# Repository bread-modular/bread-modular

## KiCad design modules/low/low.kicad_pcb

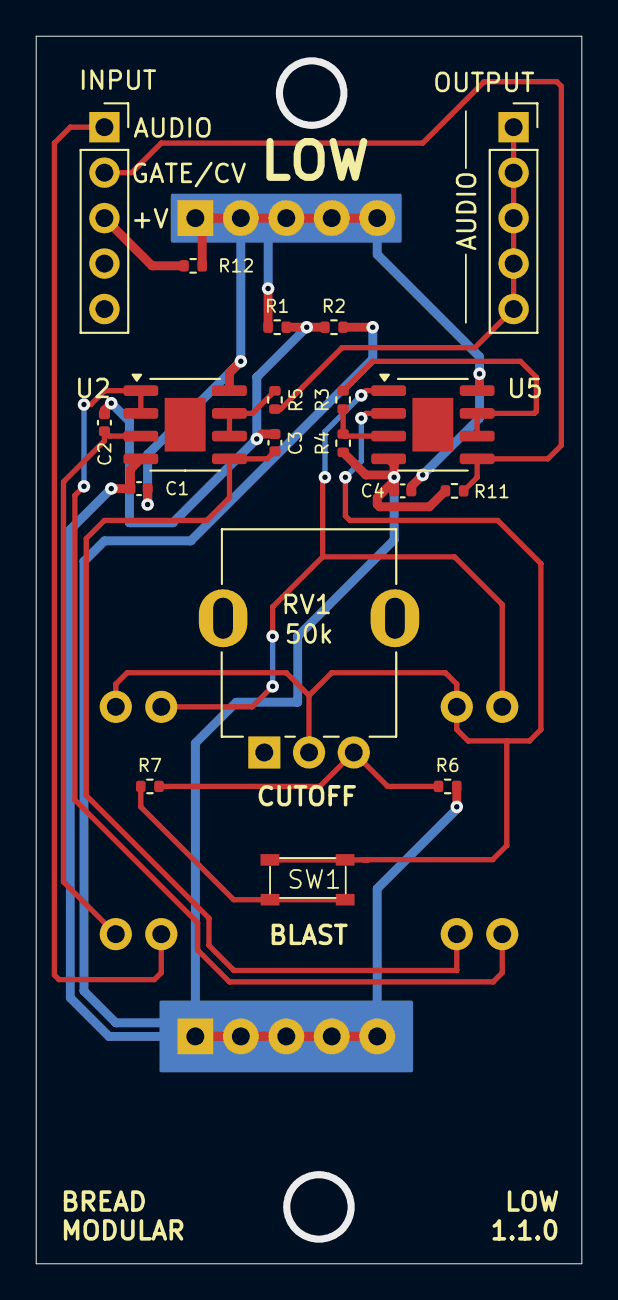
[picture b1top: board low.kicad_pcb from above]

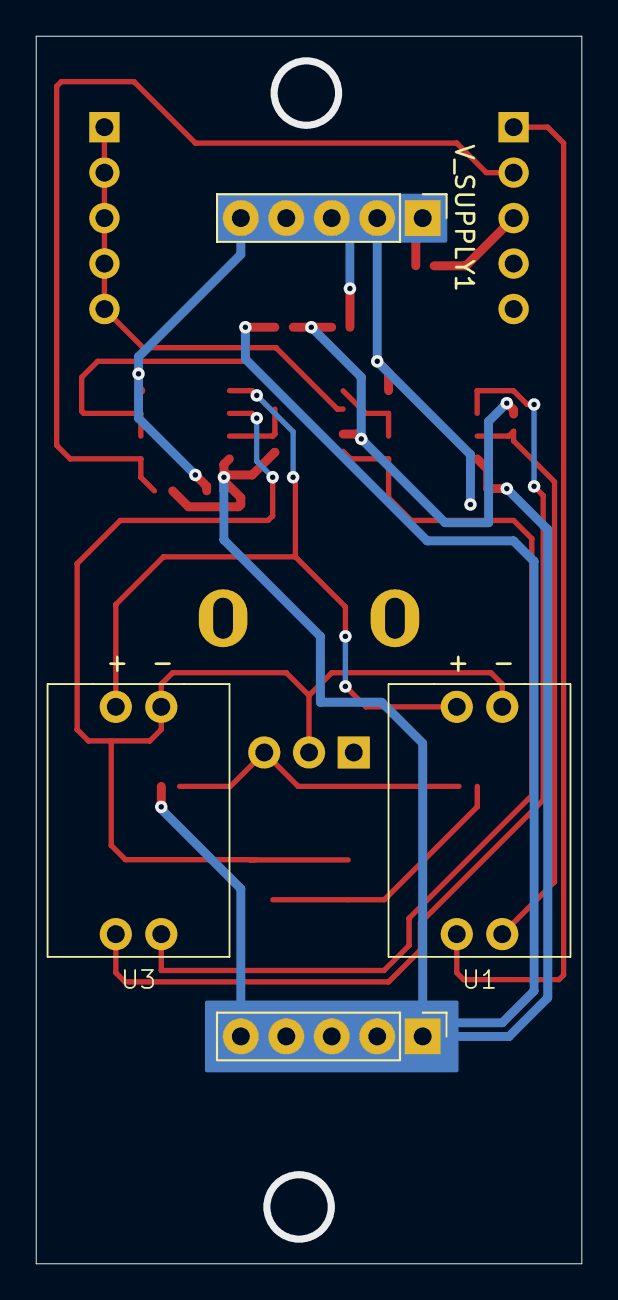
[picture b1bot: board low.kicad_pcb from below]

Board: 2 copper layers, 30.5 x 68.6 mm, 23 parts (4 on the bottom side), 17 nets.

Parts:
C1, C4: 0.1uf; C_0402_1005Metric
C2, C3: 10nf; C_0402_1005Metric
GND1: Conn_01x05_Pin; Power_Connector
INPUT1: Conn_01x05_Socket; PinSocket_1x05_P2.54mm_Vertical
OUTPUT1: Conn_01x05_Socket; PinSocket_1x05_P2.54mm_Vertical
R1, R2, R5: 1k; R_0402_1005Metric
R3, R4, R11: 1M; R_0402_1005Metric
R6, R7: 330; R_0402_1005Metric
R12: 10k; R_0402_1005Metric
RV1: 50k; Potentiometer_RV09
SW1: K2-1808SN-A4SW-01
U1, U3: VTL5C
U2, U5: MCP6002-xSN; SOIC-8-1EP_3.9x4.9mm_P1.27mm_EP2.29x3mm
V_SUPPLY1: Conn_01x05_Pin; Power_Connector

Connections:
AUDIO_IN: INPUT1.1, U1.4
AUDIO_OUT: OUTPUT1.1, OUTPUT1.2, OUTPUT1.3, OUTPUT1.4, OUTPUT1.5, R5.2
CV: INPUT1.2, R11.2, U5.5 (+)
GND: C1.2, C4.2, GND1.1, GND1.2, GND1.3, GND1.4, GND1.5, R2.2, R4.1, R6.2, R11.1, U2.4 (V-), U5.4 (V-)
unnamed: INPUT1.3, R12.2
unnamed: R6.1, R7.2, RV1.3
unnamed: R7.1, SW1.2 (B)
unnamed: C2.1, U1.3, U2.3 (+)
unnamed: U2.1, U2.2 (-), U3.4
unnamed: C3.1, U2.5 (+), U3.3
unnamed: R5.1, U2.6 (-), U2.7
unnamed: R3.1, R4.2, U5.3 (+)
unnamed: R3.2, U5.6 (-), U5.7
VAC_NEG: RV1.2, SW1.1 (A), U1.1 (-), U3.1 (-), U5.2 (-)
VAC_POS: U1.2 (+), U3.2 (+), U5.1
V_MID: C2.2, C3.2, R1.2, R2.1
V_SUPPLY: C1.1, C4.1, R1.1, R12.1, U2.8 (V+), U5.8 (V+), V_SUPPLY1.1, V_SUPPLY1.2, V_SUPPLY1.3, V_SUPPLY1.4, V_SUPPLY1.5

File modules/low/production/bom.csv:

Designator,Footprint,Quantity,Value,LCSC Part #
"C1, C4",0402,2,0.1uf,
"C2, C3",0402,2,10nf,
"GND1, V_SUPPLY1",Power_Connector,2,Conn_01x05_Pin,
"INPUT1, OUTPUT1",PinSocket_1x05_P2.54mm_Vertical,2,Conn_01x05_Socket,
"R1, R2, R5",0402,3,1k,
"R11, R3, R4",0402,3,1M,
R12,0402,1,10k,
"R6, R7",0402,2,330,
RV1,Potentiometer_RV09,1,50k,
SW1,K2-1808SN-A4SW-01,1,K2-1808SN-A4SW-01,
"U1, U3",VTL5C,2,VTL5C,
"U2, U5",SOIC-8-1EP_3.9x4.9mm_P1.27mm_EP2.29x3mm,2,MCP6002-xSN,

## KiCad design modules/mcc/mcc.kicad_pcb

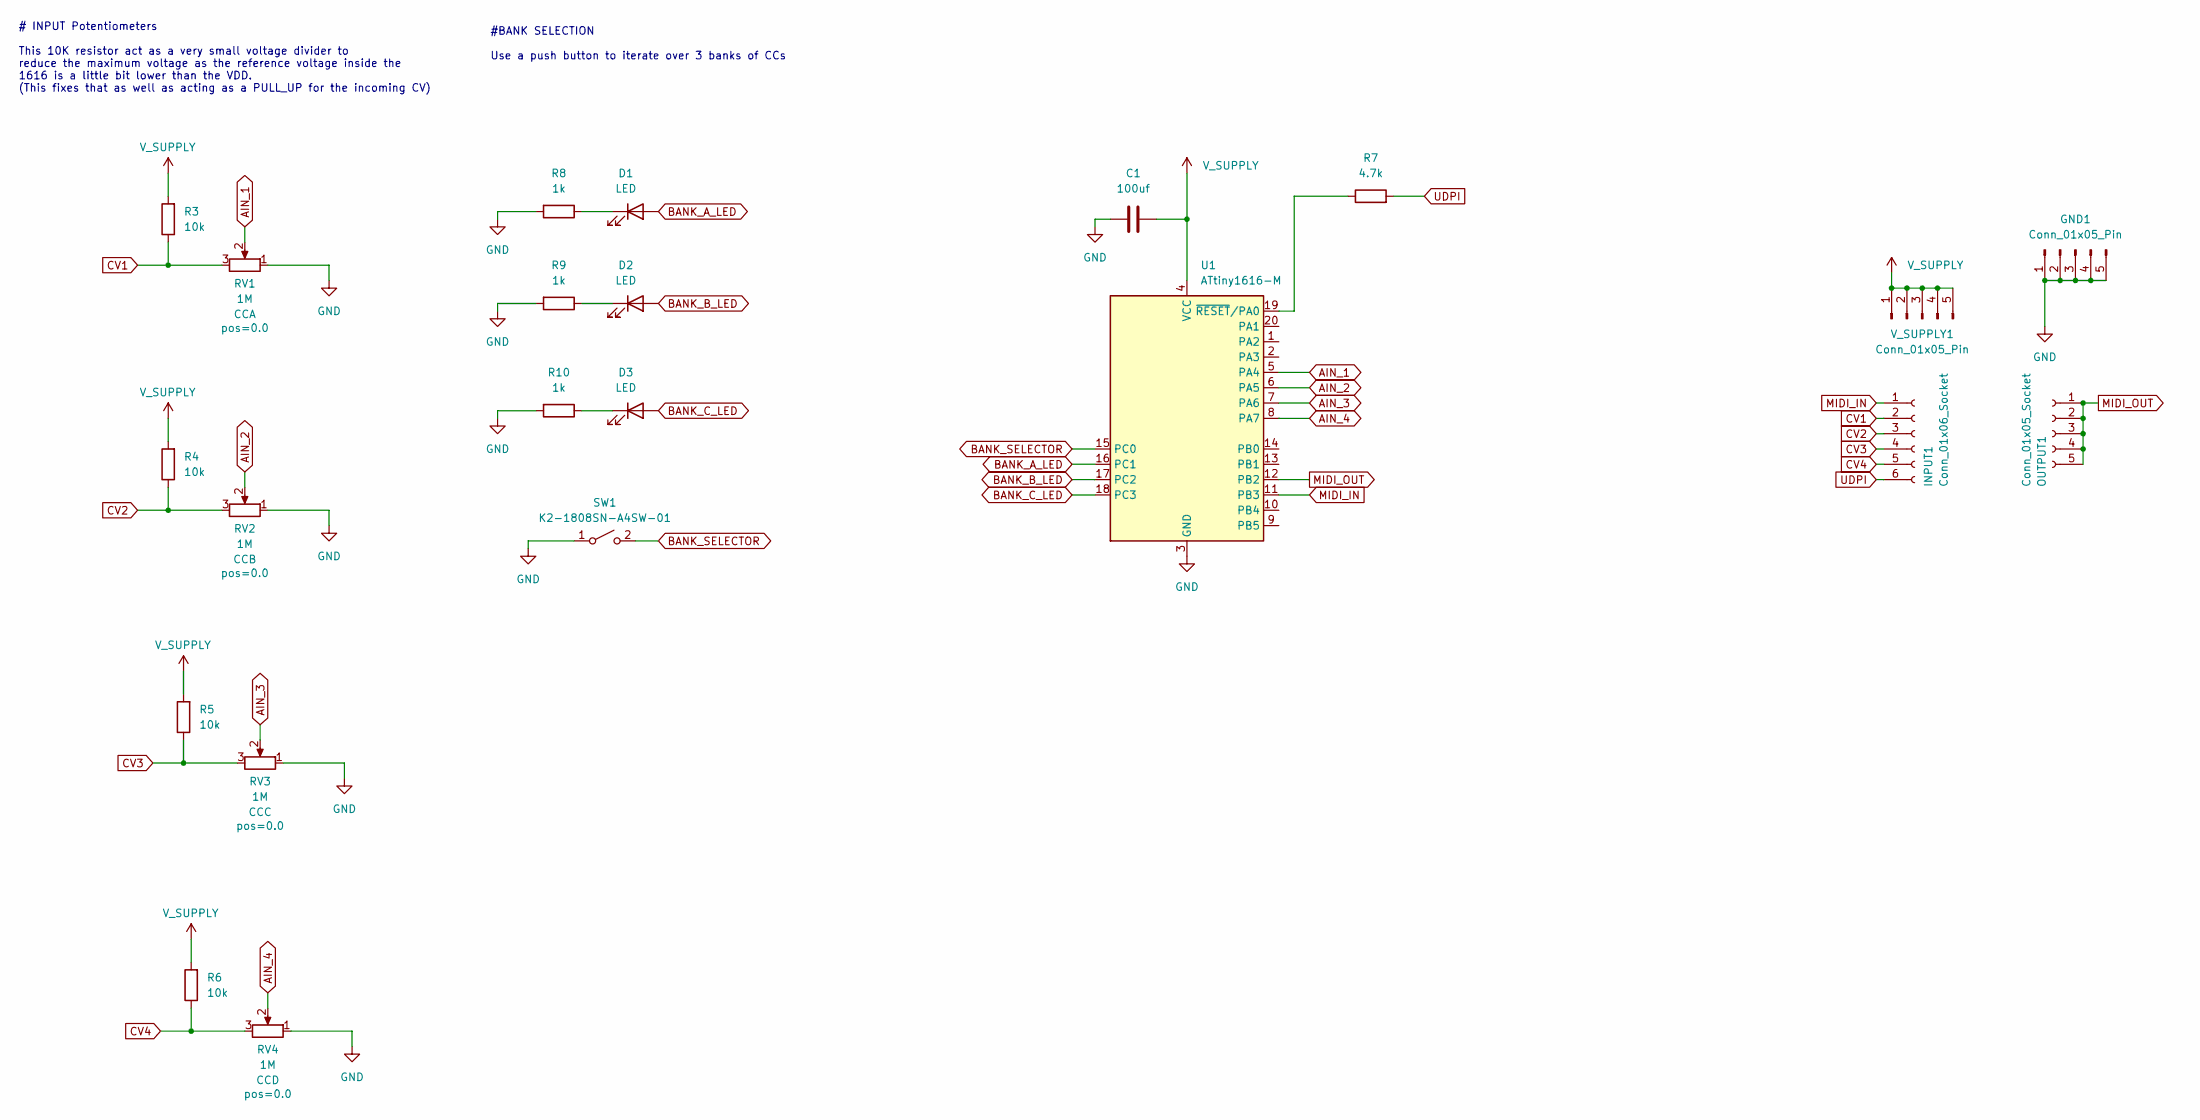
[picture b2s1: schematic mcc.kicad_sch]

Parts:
C1: 100uf; C_1206_3216Metric
D1, D2, D3: LED; LED_0603_1608Metric
GND1: Conn_01x05_Pin; Power_Connector
INPUT1: Conn_01x06_Socket; PinSocket_1x06_P2.54mm_Vertical
OUTPUT1: Conn_01x05_Socket; PinSocket_1x05_P2.54mm_Vertical
R3, R4, R5, R6: 10k; R_0402_1005Metric
R7: 4.7k; R_0402_1005Metric
R8, R9, R10: 1k; R_0402_1005Metric
RV1, RV2, RV3, RV4: 1M; Potentiometer_RV09
SW1: K2-1808SN-A4SW-01
U1: ATtiny1616-M; VQFN-20-1EP_3x3mm_P0.4mm_EP1.7x1.7mm
V_SUPPLY1: Conn_01x05_Pin; Power_Connector

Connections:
AIN_1: RV1.2, U1.5 (PA4)
AIN_2: RV2.2, U1.6 (PA5)
AIN_3: RV3.2, U1.7 (PA6)
AIN_4: RV4.2, U1.8 (PA7)
BANK_A_LED: D1.2 (A), U1.16 (PC1)
BANK_B_LED: D2.2 (A), U1.17 (PC2)
BANK_C_LED: D3.2 (A), U1.18 (PC3)
BANK_SELECTOR: SW1.2 (B), U1.15 (PC0)
CV1: INPUT1.2, R3.1, RV1.3
CV2: INPUT1.3, R4.1, RV2.3
CV3: INPUT1.4, R5.1, RV3.3
CV4: INPUT1.5, R6.1, RV4.3
GND: C1.1, GND1.1, GND1.2, GND1.3, GND1.4, GND1.5, R8.2, R9.2, R10.2, RV1.1, RV2.1, RV3.1, RV4.1, SW1.1 (A), U1.3 (GND), U1.21 (GND)
MIDI_IN: INPUT1.1, U1.11 (PB3)
MIDI_OUT: OUTPUT1.1, OUTPUT1.2, OUTPUT1.3, OUTPUT1.4, OUTPUT1.5, U1.12 (PB2)
unnamed: D1.1 (K), R8.1
unnamed: D2.1 (K), R9.1
unnamed: D3.1 (K), R10.1
unnamed: R7.1, U1.19 (~RESET/PA0)
UDPI: INPUT1.6, R7.2
V_SUPPLY: C1.2, R3.2, R4.2, R5.2, R6.2, U1.4 (VCC), V_SUPPLY1.1, V_SUPPLY1.2, V_SUPPLY1.3, V_SUPPLY1.4, V_SUPPLY1.5

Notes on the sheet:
# INPUT Potentiometers This 10K resistor act as a very small voltage divider to reduce the maximum voltage as the reference voltage inside the 1616 is a little bit lower than the VDD. (This fixes that as well as acting as a PULL_UP for the incoming CV)
#BANK SELECTION Use a push button to iterate over 3 banks of CCs

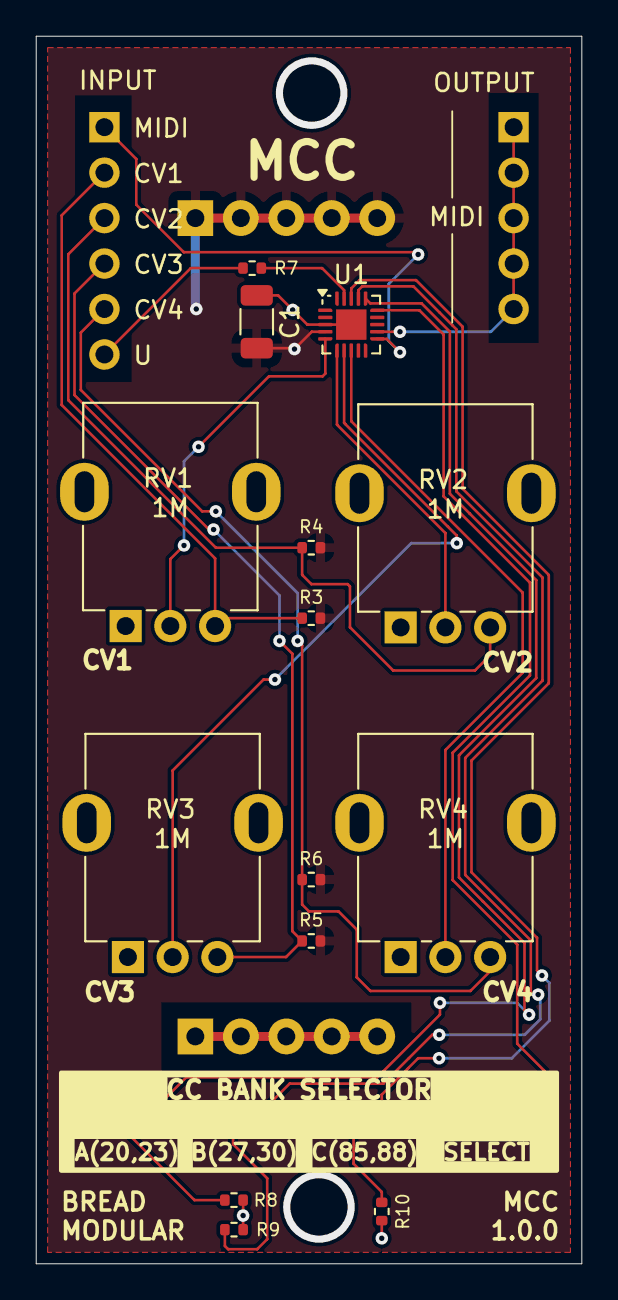
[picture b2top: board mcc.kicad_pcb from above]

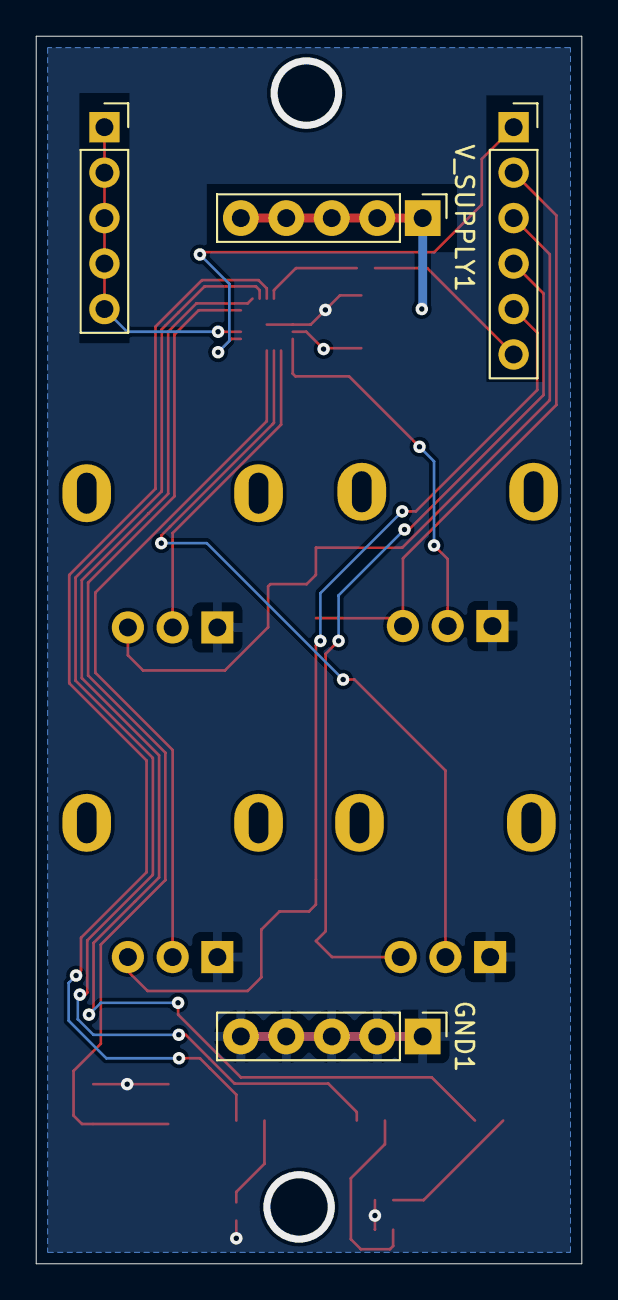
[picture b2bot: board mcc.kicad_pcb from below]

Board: 2 copper layers, 30.5 x 68.6 mm, 22 parts (4 on the bottom side), 21 nets.

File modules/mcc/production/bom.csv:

Designator,Footprint,Quantity,Value,LCSC Part #
C1,1206,1,100uf,
"D1, D2, D3",0603,3,LED,
"GND1, V_SUPPLY1",Power_Connector,2,Conn_01x05_Pin,
INPUT1,PinSocket_1x06_P2.54mm_Vertical,1,Conn_01x06_Socket,
OUTPUT1,PinSocket_1x05_P2.54mm_Vertical,1,Conn_01x05_Socket,
"R10, R8, R9",0402,3,1k,
"R3, R4, R5, R6",0402,4,10k,
R7,0402,1,4.7k,
"RV1, RV2, RV3, RV4",Potentiometer_RV09,4,1M,
SW1,K2-1808SN-A4SW-01,1,K2-1808SN-A4SW-01,
U1,VQFN-20-1EP_3x3mm_P0.4mm_EP1.7x1.7mm,1,ATtiny1616-M,

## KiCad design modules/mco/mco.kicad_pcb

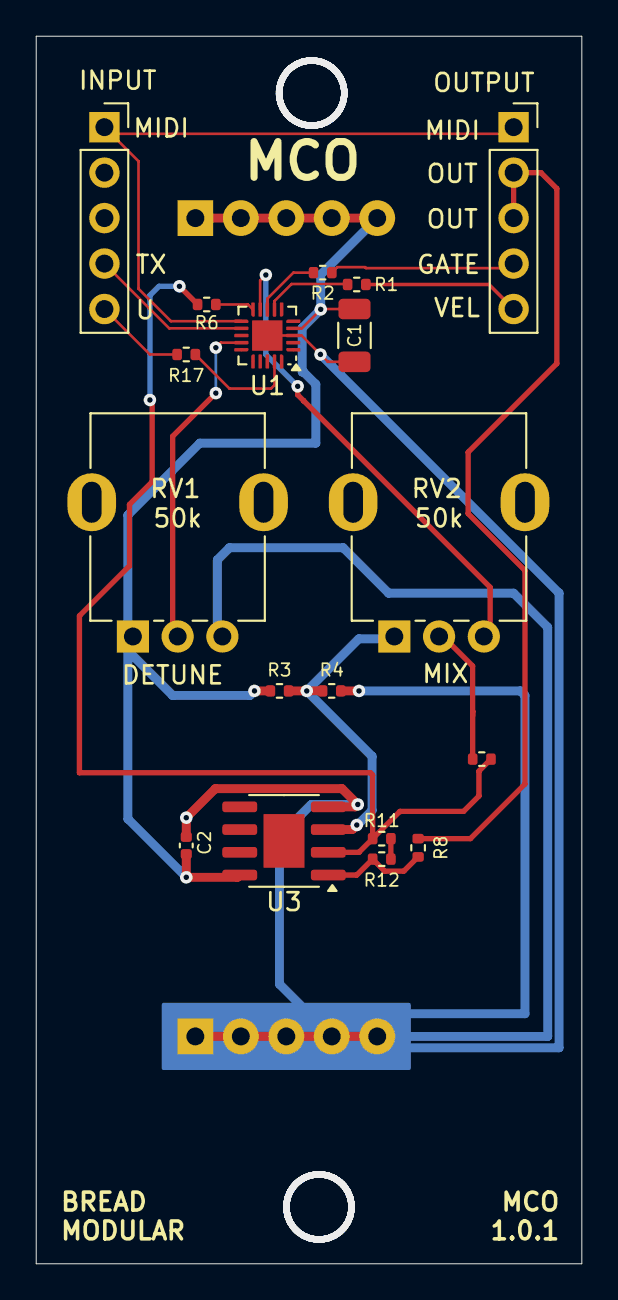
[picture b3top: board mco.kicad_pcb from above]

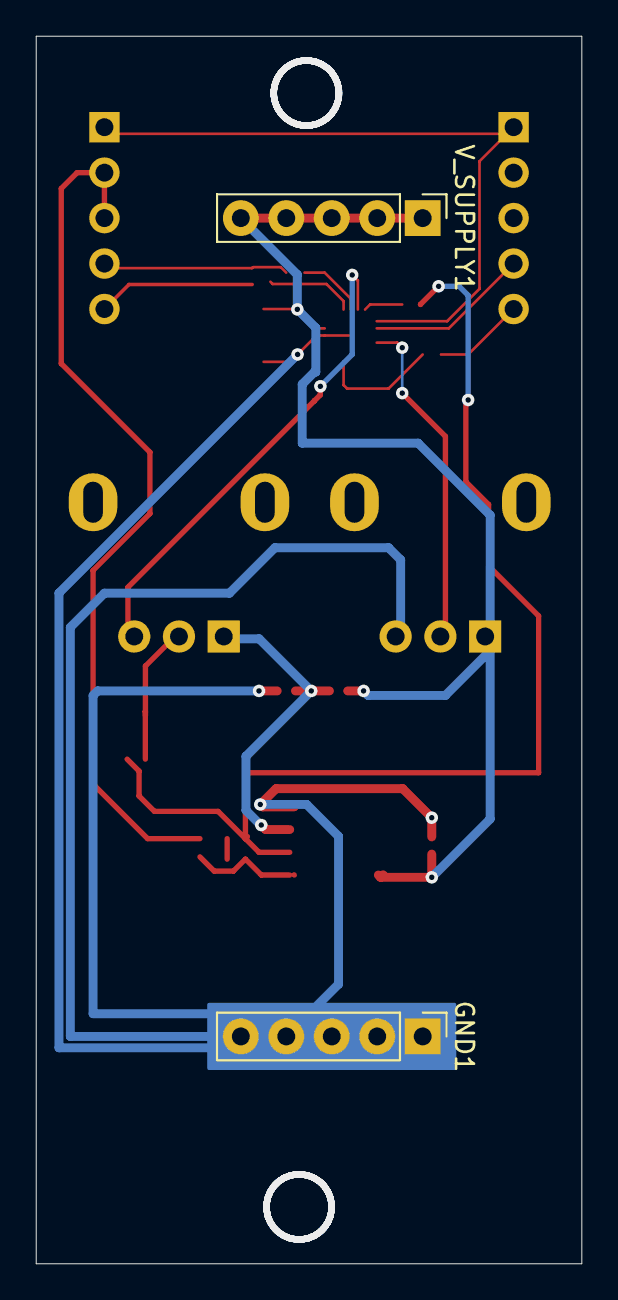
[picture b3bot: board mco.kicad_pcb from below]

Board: 2 copper layers, 30.5 x 68.6 mm, 20 parts (2 on the bottom side), 19 nets.

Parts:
C1: 100uf; C_1206_3216Metric
C2: 0.1uf; C_0402_1005Metric
GND1: Conn_01x05_Pin; Power_Connector
INPUT1: Conn_01x05_Socket; PinSocket_1x05_P2.54mm_Vertical
OUTPUT1: Conn_01x05_Socket; PinSocket_1x05_P2.54mm_Vertical
R1, R2, R3, R4, R8: 1k; R_0402_1005Metric
R6, R10: 1M; R_0402_1005Metric
R11, R12: 200k; R_0402_1005Metric
R17: 4.7k; R_0402_1005Metric
RV1, RV2: 50k; Potentiometer_RV09
U1: ATtiny1616-M; VQFN-20-1EP_3x3mm_P0.4mm_EP1.7x1.7mm
U3: MCP6002-xSN; SOIC-8-1EP_3.9x4.9mm_P1.27mm_EP2.29x3mm
V_SUPPLY1: Conn_01x05_Pin; Power_Connector

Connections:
DETUNED_TONE: RV2.3, U1.9 (PB5)
FUNDAMENTAL_TONE: R6.1, U1.10 (PB4)
GATE: OUTPUT1.4, R2.2
GND: C1.1, C2.2, GND1.1, GND1.2, GND1.3, GND1.4, GND1.5, R4.2, RV1.3, U1.3 (GND), U1.21 (GND), U3.4 (V-)
MIDI: INPUT1.1, OUTPUT1.1, U1.11 (PB3)
MIX_OUT: OUTPUT1.2, OUTPUT1.3, R8.2
unnamed: R10.1, RV2.2
unnamed: R11.2, R12.1
unnamed: R8.1, R12.2, U3.1
unnamed: R1.1, U1.7 (PA6)
unnamed: R2.1, U1.8 (PA7)
unnamed: R17.1, U1.19 (~RESET/PA0)
unnamed: R6.2, R10.2, R11.1, U3.2 (-)
TX: INPUT1.4, U1.12 (PB2)
UDPI: INPUT1.5, R17.2
VELOCITY: OUTPUT1.5, R1.2
V_DETUNED: RV1.2, U1.14 (PB0)
V_MID: R3.2, R4.1, RV2.1, U3.3 (+)
V_SUPPLY: C1.2, C2.1, R3.1, RV1.1, U1.4 (VCC), U3.8 (V+), V_SUPPLY1.1, V_SUPPLY1.2, V_SUPPLY1.3, V_SUPPLY1.4, V_SUPPLY1.5

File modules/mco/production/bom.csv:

Designator,Footprint,Quantity,Value,LCSC Part #
C1,1206,1,100uf,
C2,0402,1,0.1uf,
"GND1, V_SUPPLY1",Power_Connector,2,Conn_01x05_Pin,
"INPUT1, OUTPUT1",PinSocket_1x05_P2.54mm_Vertical,2,Conn_01x05_Socket,
"R1, R2, R3, R4, R8",0402,5,1k,
"R10, R6",0402,2,1M,
"R11, R12",0402,2,200k,
R17,0402,1,4.7k,
"RV1, RV2",Potentiometer_RV09,2,50k,
U1,VQFN-20-1EP_3x3mm_P0.4mm_EP1.7x1.7mm,1,ATtiny1616-M,
U3,SOIC-8-1EP_3.9x4.9mm_P1.27mm_EP2.29x3mm,1,MCP6002-xSN,

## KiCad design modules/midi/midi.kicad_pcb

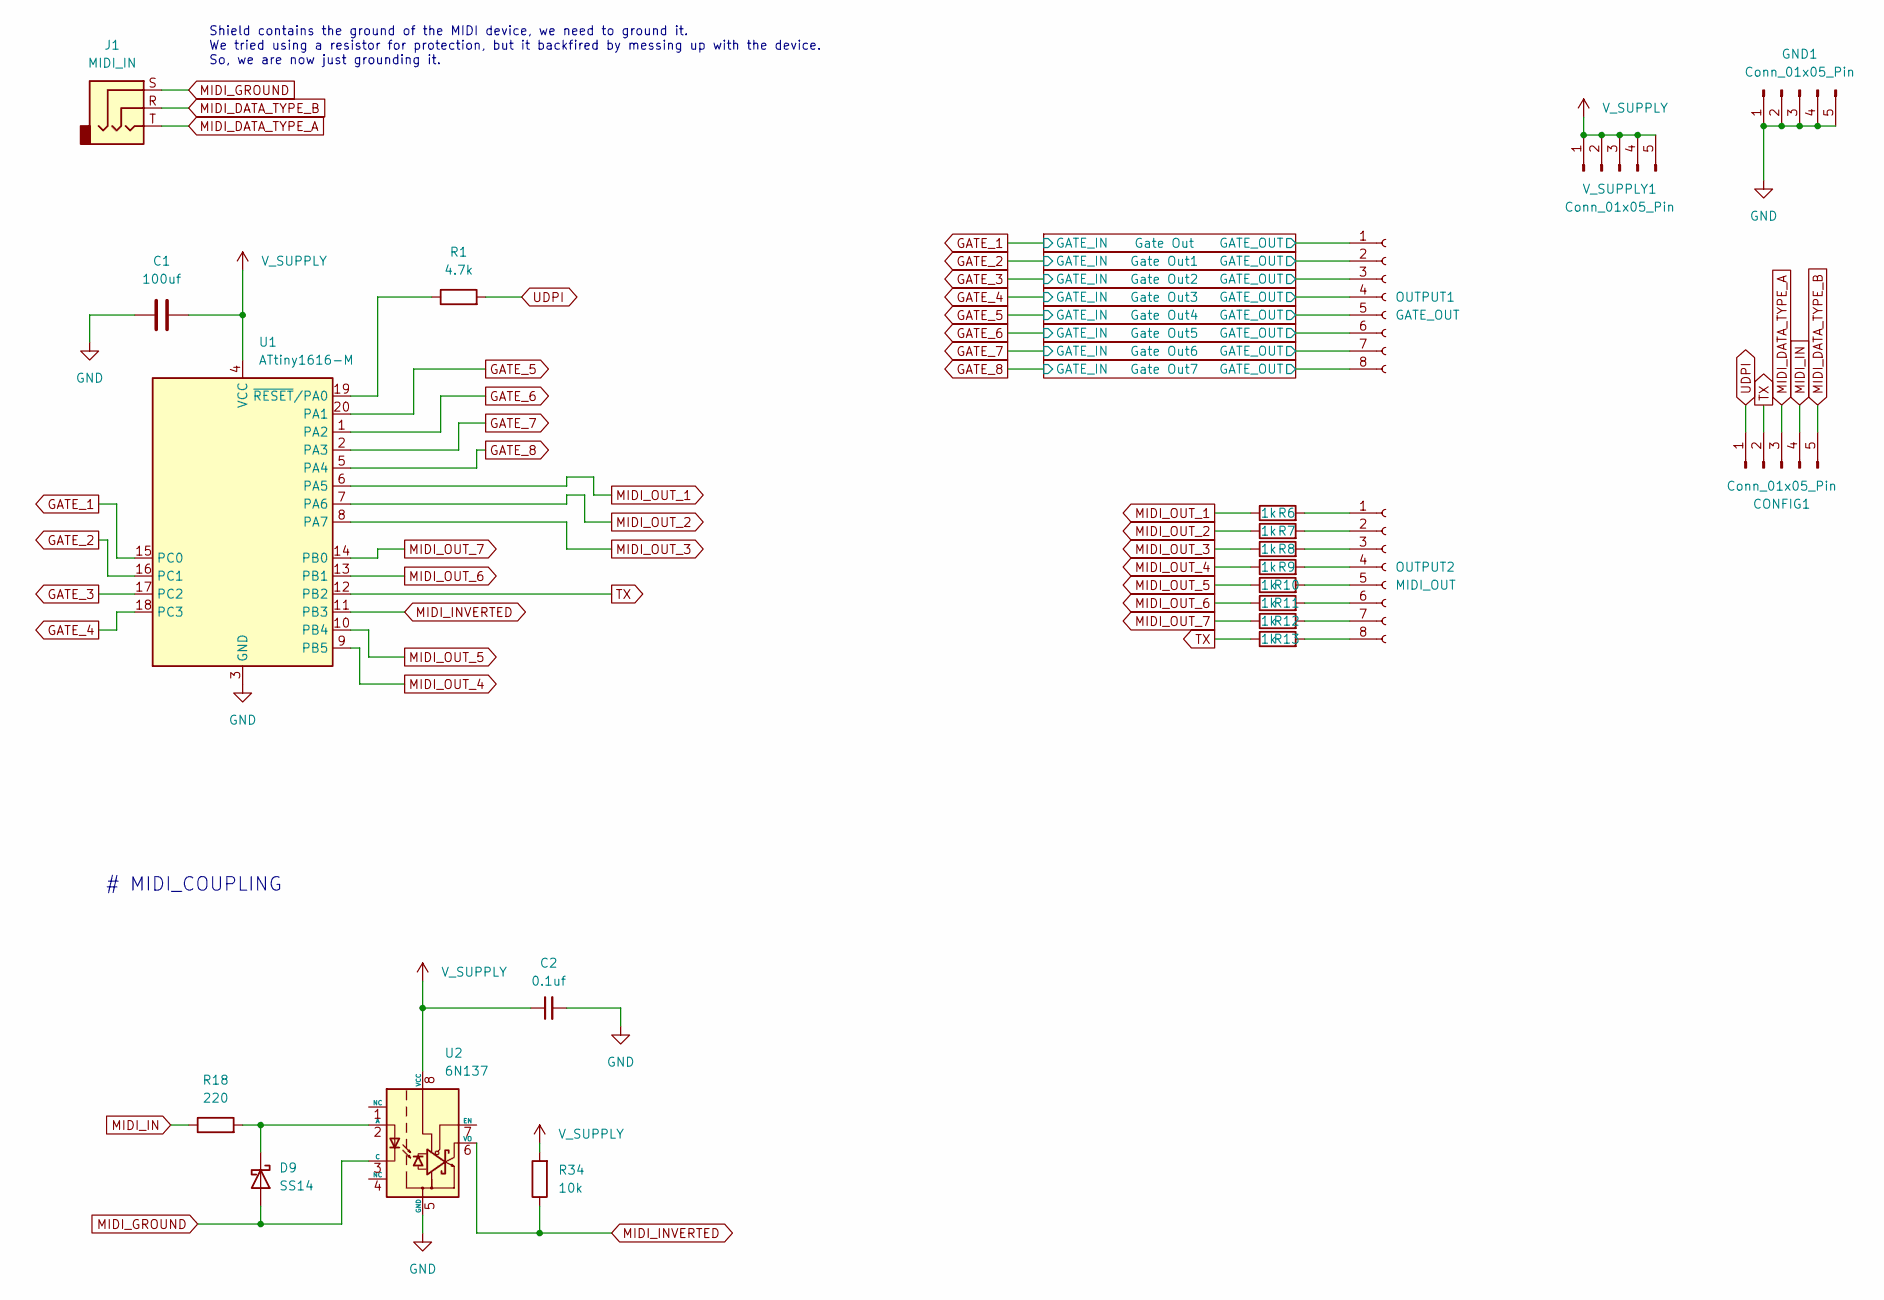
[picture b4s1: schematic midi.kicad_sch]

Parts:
C1: 100uf; C_1206_3216Metric
C2: 0.1uf; C_0402_1005Metric
CONFIG1: Conn_01x05_Pin; Power_Connector
D9: SS14; D_SMA
GND1: Conn_01x05_Pin; Power_Connector
J1: MIDI_IN; Jack_3.5mm_QingPu_WQP-PJ366ST_Vertical
OUTPUT1: GATE_OUT; PinSocket_1x08_P2.54mm_Vertical
OUTPUT2: MIDI_OUT; PinSocket_1x08_P2.54mm_Vertical
R1: 4.7k; R_0402_1005Metric
R6, R7, R8, R9, R10, R11, R12, R13: 1k; R_0402_1005Metric
R18: 220; R_0402_1005Metric
R34: 10k; R_0402_1005Metric
U1: ATtiny1616-M; VQFN-20-1EP_3x3mm_P0.4mm_EP1.7x1.7mm
U2: 6N137; SOIC-8 2.54
V_SUPPLY1: Conn_01x05_Pin; Power_Connector

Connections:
/Gate Out1/GATE_OUT: OUTPUT1.2; also elsewhere on the board
/Gate Out2/GATE_OUT: OUTPUT1.3; also elsewhere on the board
/Gate Out3/GATE_OUT: OUTPUT1.4; also elsewhere on the board
/Gate Out4/GATE_OUT: OUTPUT1.5; also elsewhere on the board
/Gate Out5/GATE_OUT: OUTPUT1.6; also elsewhere on the board
/Gate Out6/GATE_OUT: OUTPUT1.7; also elsewhere on the board
/Gate Out7/GATE_OUT: OUTPUT1.8; also elsewhere on the board
/Gate Out/GATE_OUT: OUTPUT1.1; also elsewhere on the board
GATE_1: U1.15 (PC0); also elsewhere on the board
GATE_2: U1.16 (PC1); also elsewhere on the board
GATE_3: U1.17 (PC2); also elsewhere on the board
GATE_4: U1.18 (PC3); also elsewhere on the board
GATE_5: U1.20 (PA1); also elsewhere on the board
GATE_6: U1.1 (PA2); also elsewhere on the board
GATE_7: U1.2 (PA3); also elsewhere on the board
GATE_8: U1.5 (PA4); also elsewhere on the board
GND: C1.1, C2.2, GND1.1, GND1.2, GND1.3, GND1.4, GND1.5, U1.3 (GND), U1.21 (GND), U2.5 (GND); also elsewhere on the board
MIDI_DATA_TYPE_A: CONFIG1.3, J1.T
MIDI_DATA_TYPE_B: CONFIG1.5, J1.R
MIDI_GROUND: D9.2 (A), J1.S, U2.3 (C)
MIDI_IN: CONFIG1.4, R18.1
MIDI_INVERTED: R34.1, U1.11 (PB3), U2.6 (VO)
MIDI_OUT_1: R6.1, U1.6 (PA5)
MIDI_OUT_2: R7.1, U1.7 (PA6)
MIDI_OUT_3: R8.1, U1.8 (PA7)
MIDI_OUT_4: R9.1, U1.9 (PB5)
MIDI_OUT_5: R10.1, U1.10 (PB4)
MIDI_OUT_6: R11.1, U1.13 (PB1)
MIDI_OUT_7: R12.1, U1.14 (PB0)
unnamed: D9.1 (K), R18.2, U2.2 (A)
unnamed: OUTPUT2.1, R6.2
unnamed: OUTPUT2.2, R7.2
unnamed: OUTPUT2.3, R8.2
unnamed: OUTPUT2.4, R9.2
unnamed: OUTPUT2.5, R10.2
unnamed: OUTPUT2.6, R11.2
unnamed: OUTPUT2.7, R12.2
unnamed: OUTPUT2.8, R13.2
unnamed: R1.1, U1.19 (~RESET/PA0)
TX: CONFIG1.2, R13.1, U1.12 (PB2)
UDPI: CONFIG1.1, R1.2
V_SUPPLY: C1.2, C2.1, R34.2, U1.4 (VCC), U2.8 (VCC), V_SUPPLY1.1, V_SUPPLY1.2, V_SUPPLY1.3, V_SUPPLY1.4, V_SUPPLY1.5; also elsewhere on the board

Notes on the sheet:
# MIDI_COUPLING
Shield contains the ground of the MIDI device, we need to ground it. We tried using a resistor for protection, but it backfired by messing up with the device. So, we are now just grounding it.

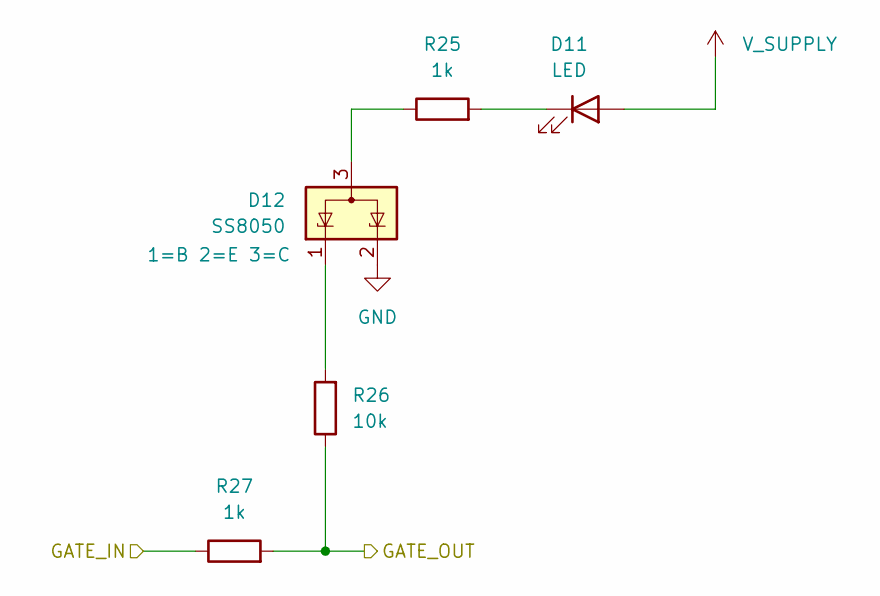
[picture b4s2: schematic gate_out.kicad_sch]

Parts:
D11: LED; LED_0603_1608Metric
D12: SS8050; SOT-23
R25, R27: 1k; R_0402_1005Metric
R26: 10k; R_0402_1005Metric

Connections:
/Gate Out5/GATE_OUT: R26.1, R27.2; also elsewhere on the board
GATE_6: R27.1; also elsewhere on the board
GND: D12.2 (K); also elsewhere on the board
unnamed: D11.1 (K), R25.2
unnamed: D12.3 (A), R25.1
unnamed: D12.1 (K), R26.2
V_SUPPLY: D11.2 (A); also elsewhere on the board

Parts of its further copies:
D1, D4, D6, D8, D13, D15, D100: LED; LED_0603_1608Metric
D2, D3, D5, D7, D10, D14, D16: SS8050; SOT-23
R2, R4, R14, R15, R17, R19, R21, R22, R24, R28, R30, R31, R33, R44: 1k; R_0402_1005Metric
R3, R5, R16, R20, R23, R29, R32: 10k; R_0402_1005Metric

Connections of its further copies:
/Gate Out1/GATE_OUT: R3.1, R14.2; also elsewhere on the board
/Gate Out2/GATE_OUT: R16.1, R17.2; also elsewhere on the board
/Gate Out3/GATE_OUT: R20.1, R21.2; also elsewhere on the board
/Gate Out4/GATE_OUT: R23.1, R24.2; also elsewhere on the board
/Gate Out6/GATE_OUT: R29.1, R30.2; also elsewhere on the board
/Gate Out7/GATE_OUT: R32.1, R33.2; also elsewhere on the board
/Gate Out/GATE_OUT: R5.1, R44.2; also elsewhere on the board
GATE_1: R44.1; also elsewhere on the board
GATE_2: R14.1; also elsewhere on the board
GATE_3: R17.1; also elsewhere on the board
GATE_4: R21.1; also elsewhere on the board
GATE_5: R24.1; also elsewhere on the board
GATE_7: R30.1; also elsewhere on the board
GATE_8: R33.1; also elsewhere on the board
GND: D2.2 (K), D3.2 (K), D5.2 (K), D7.2 (K), D10.2 (K), D14.2 (K), D16.2 (K); also elsewhere on the board
unnamed: D1.1 (K), R2.2
unnamed: D2.3 (A), R4.1
unnamed: D2.1 (K), R5.2
unnamed: D3.3 (A), R2.1
unnamed: D3.1 (K), R3.2
unnamed: D4.1 (K), R15.2
unnamed: D5.3 (A), R15.1
unnamed: D5.1 (K), R16.2
unnamed: D6.1 (K), R19.2
unnamed: D7.3 (A), R19.1
unnamed: D7.1 (K), R20.2
unnamed: D8.1 (K), R22.2
unnamed: D10.3 (A), R22.1
unnamed: D10.1 (K), R23.2
unnamed: D13.1 (K), R28.2
unnamed: D14.3 (A), R28.1
unnamed: D14.1 (K), R29.2
unnamed: D15.1 (K), R31.2
unnamed: D16.3 (A), R31.1
unnamed: D16.1 (K), R32.2
unnamed: D100.1 (K), R4.2
V_SUPPLY: D1.2 (A), D4.2 (A), D6.2 (A), D8.2 (A), D13.2 (A), D15.2 (A), D100.2 (A); also elsewhere on the board

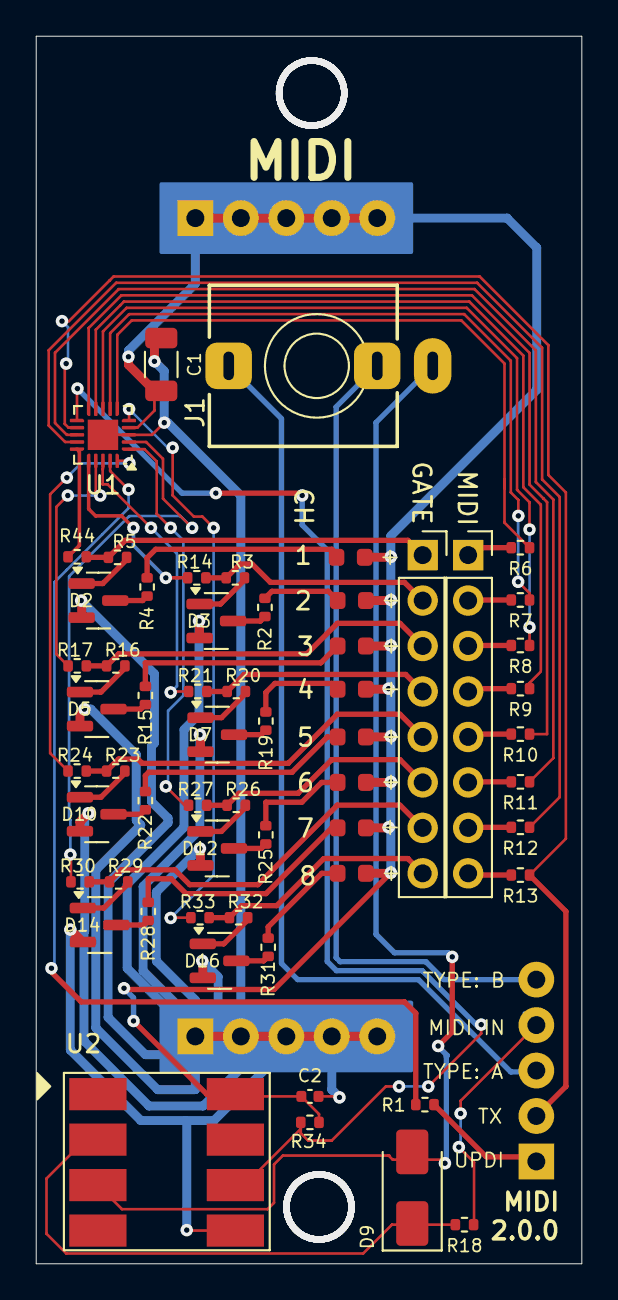
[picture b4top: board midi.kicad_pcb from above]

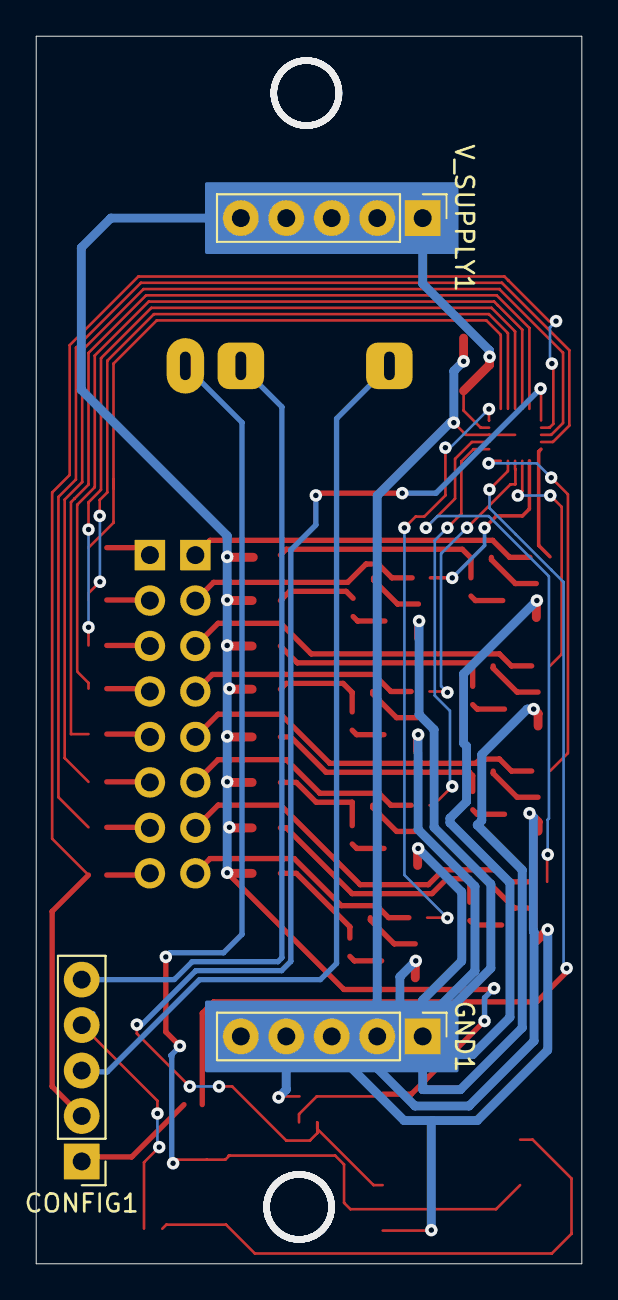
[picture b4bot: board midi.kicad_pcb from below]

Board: 2 copper layers, 30.5 x 68.6 mm, 62 parts (3 on the bottom side), 66 nets.

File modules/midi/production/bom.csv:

Designator,Footprint,Quantity,Value,LCSC Part #
C1,1206,1,100uf,
C2,0402,1,0.1uf,
"CONFIG1, GND1, V_SUPPLY1",Power_Connector,3,Conn_01x05_Pin,
"D1, D100, D11, D13, D15, D4, D6, D8",0603,8,LED,
"D10, D12, D14, D16, D2, D3, D5, D7",SOT-23,8,SS8050,
D9,D_SMA,1,SS14,
J1,Jack_3.5mm_QingPu_WQP-PJ366ST_Vertical,1,MIDI_IN,
OUTPUT1,PinSocket_1x08_P2.54mm_Vertical,1,GATE_OUT,
OUTPUT2,PinSocket_1x08_P2.54mm_Vertical,1,MIDI_OUT,
R1,0402,1,4.7k,
"R10, R11, R12, R13, R14, R15, R17, R19, R2, R21, R22, R24, R25, R27, R28, R30, R31, R33, R4, R44, R6, R7, R8, R9",0402,24,1k,
"R16, R20, R23, R26, R29, R3, R32, R34, R5",0402,9,10k,
R18,0402,1,220,
U1,VQFN-20-1EP_3x3mm_P0.4mm_EP1.7x1.7mm,1,ATtiny1616-M,
U2,SOIC-8 2.54,1,6N137,

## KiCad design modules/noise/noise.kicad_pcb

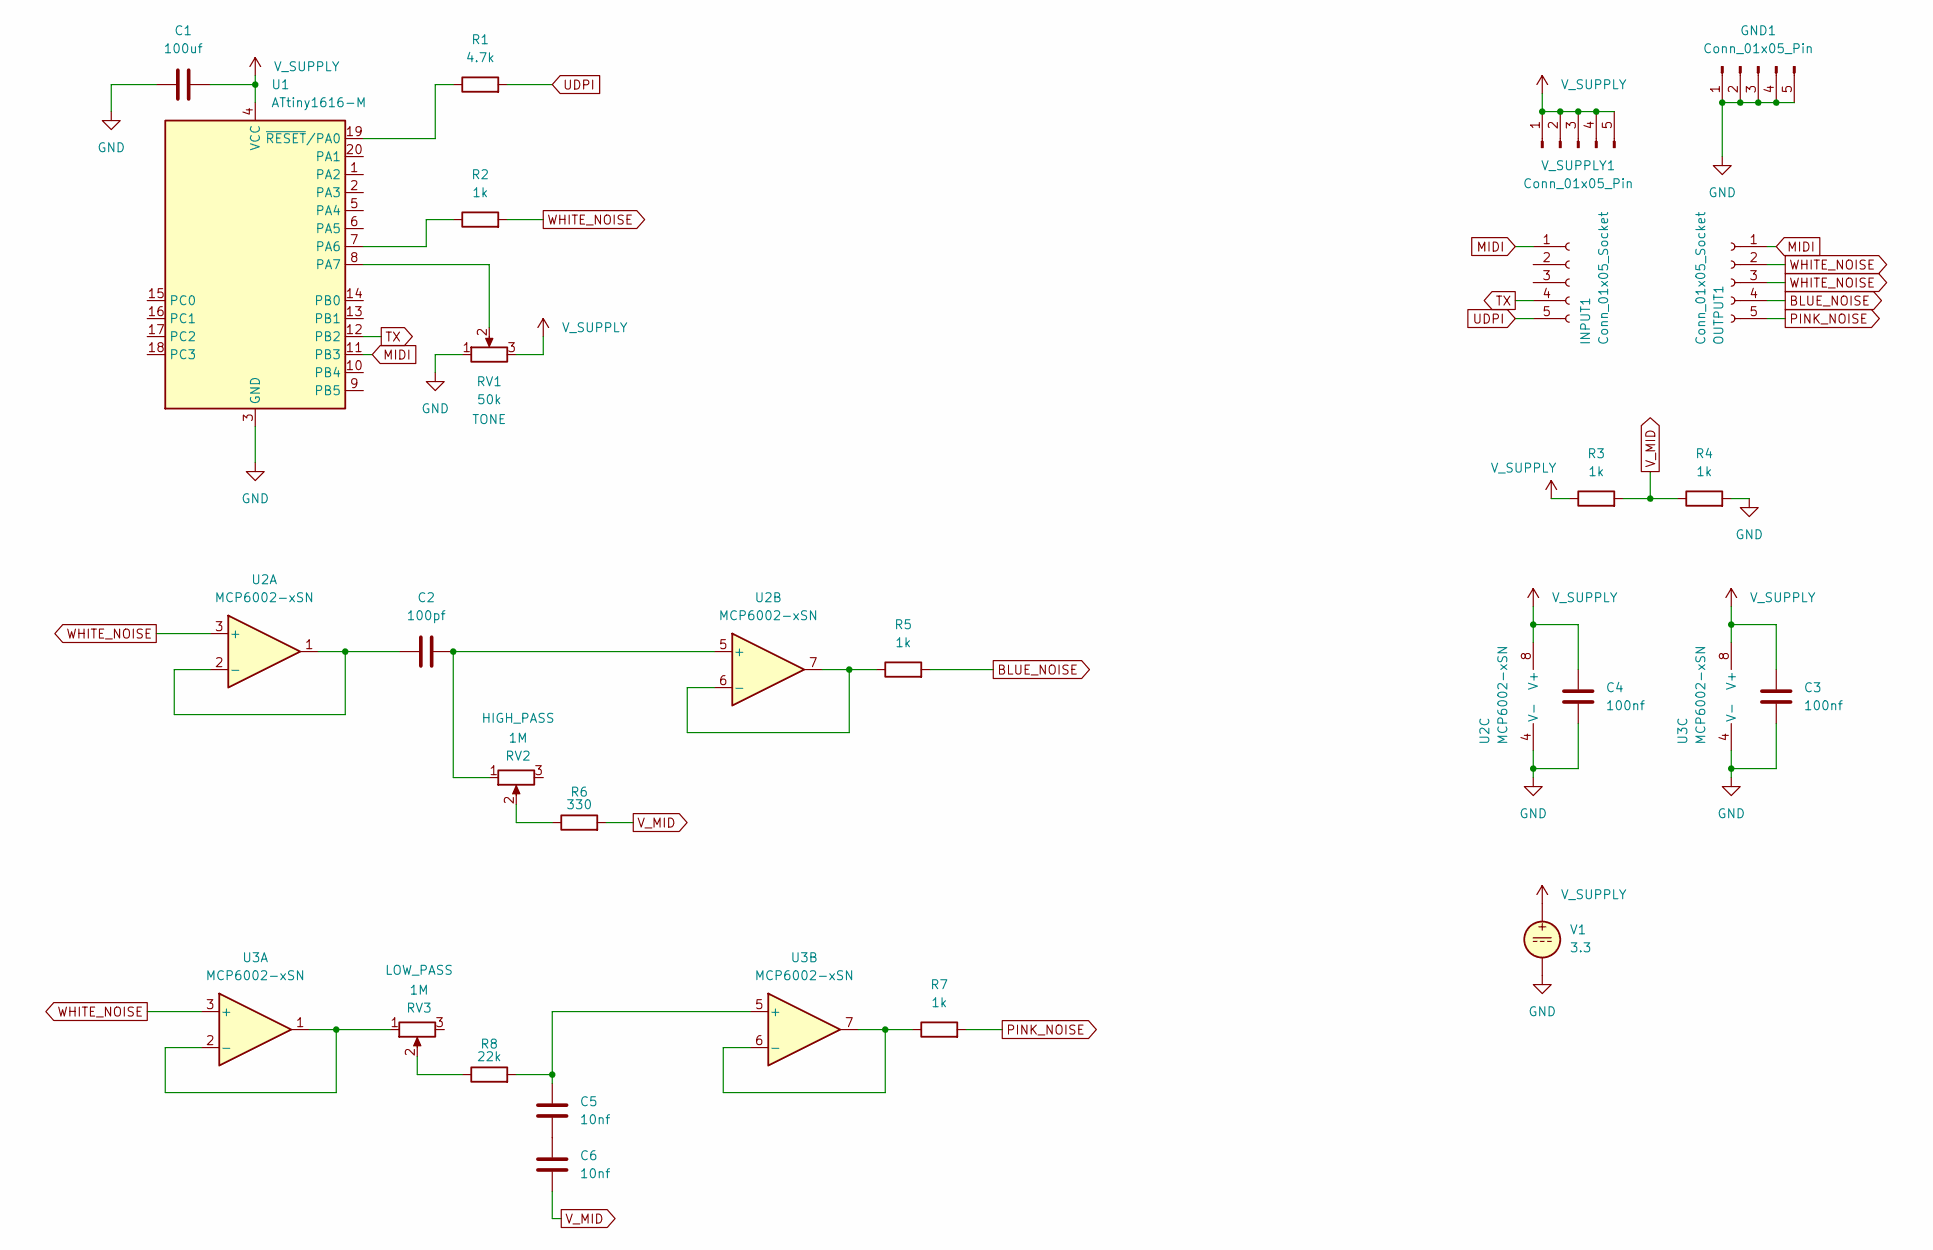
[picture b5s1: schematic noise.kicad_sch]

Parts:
C1: 100uf; C_1206_3216Metric
C2: 100pf; C_0402_1005Metric
C3, C4: 100nf; C_0402_1005Metric
C5, C6: 10nf; C_0402_1005Metric
GND1: Conn_01x05_Pin; Power_Connector
INPUT1: Conn_01x05_Socket; PinSocket_1x05_P2.54mm_Vertical
OUTPUT1: Conn_01x05_Socket; PinSocket_1x05_P2.54mm_Vertical
R1: 4.7k; R_0402_1005Metric
R2, R3, R4, R5, R7: 1k; R_0402_1005Metric
R6: 330; R_0402_1005Metric
R8: 22k; R_0402_1005Metric
RV1: 50k; Potentiometer_RV09
RV2, RV3: 1M; Potentiometer_RV09
U1: ATtiny1616-M; VQFN-20-1EP_3x3mm_P0.4mm_EP1.7x1.7mm
U2, U3: MCP6002-xSN; SOIC-8-1EP_3.9x4.9mm_P1.27mm_EP2.29x3mm
V1: 3.3
V_SUPPLY1: Conn_01x05_Pin; Power_Connector

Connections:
BLUE_NOISE: OUTPUT1.4, R5.2
GND: C1.1, C3.1, C4.1, GND1.1, GND1.2, GND1.3, GND1.4, GND1.5, R4.2, RV1.1, U1.3 (GND), U1.21 (GND), U2.4 (V-), U3.4 (V-), V1.2
MIDI: INPUT1.1, OUTPUT1.1, U1.11 (PB3)
unnamed: C5.1, C6.2
unnamed: R6.1, RV2.2
unnamed: R8.1, RV3.2
unnamed: R2.1, U1.7 (PA6)
unnamed: RV1.2, U1.8 (PA7)
unnamed: R1.1, U1.19 (~RESET/PA0)
unnamed: C2.1, U2.1, U2.2 (-)
unnamed: C2.2, RV2.1, U2.5 (+)
unnamed: R5.1, U2.6 (-), U2.7
unnamed: RV3.1, U3.1, U3.2 (-)
unnamed: C5.2, R8.2, U3.5 (+)
unnamed: R7.1, U3.6 (-), U3.7
PINK_NOISE: OUTPUT1.5, R7.2
TX: INPUT1.4, U1.12 (PB2)
UDPI: INPUT1.5, R1.2
V_MID: C6.1, R3.2, R4.1, R6.2
V_SUPPLY: C1.2, C3.2, C4.2, R3.1, RV1.3, U1.4 (VCC), U2.8 (V+), U3.8 (V+), V1.1, V_SUPPLY1.1, V_SUPPLY1.2, V_SUPPLY1.3, V_SUPPLY1.4, V_SUPPLY1.5
WHITE_NOISE: OUTPUT1.2, OUTPUT1.3, R2.2, U2.3 (+), U3.3 (+)
